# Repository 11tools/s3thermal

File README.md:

# s3thermal
a iray thermal camera controller pcb use Allwinner S3 

Can record thermal video. take thermal picture. may support night vision fusion in future

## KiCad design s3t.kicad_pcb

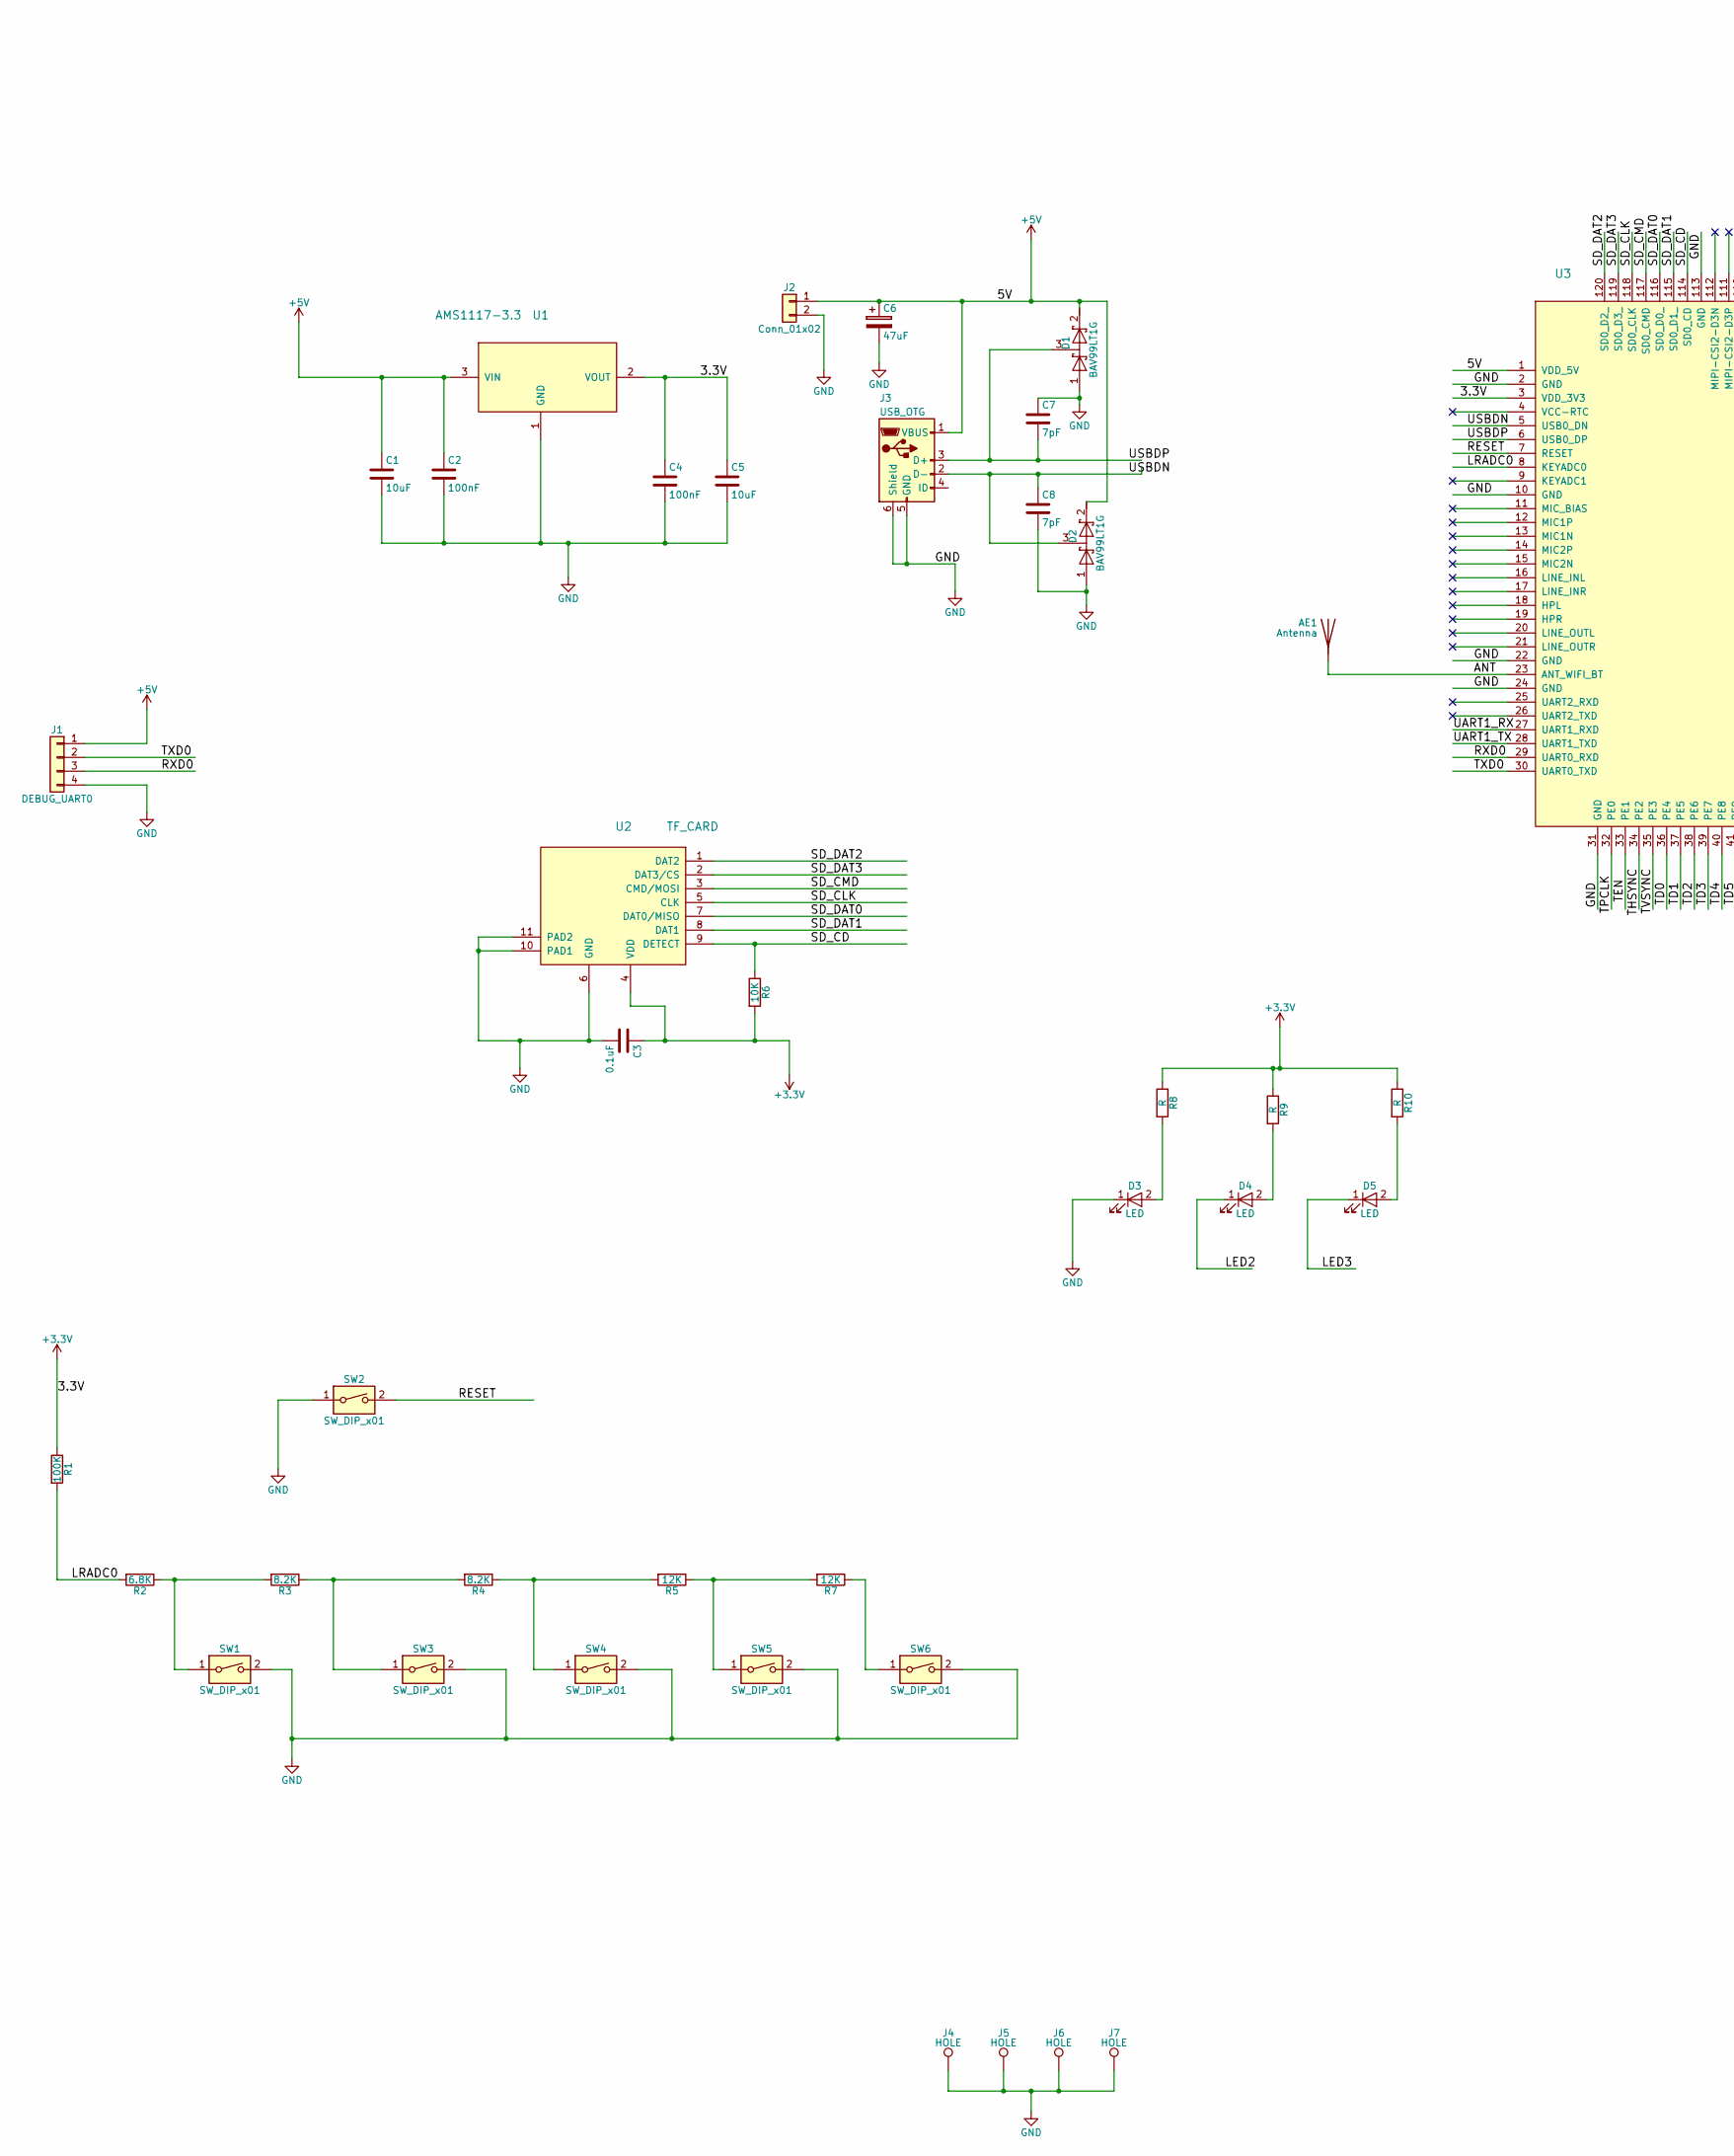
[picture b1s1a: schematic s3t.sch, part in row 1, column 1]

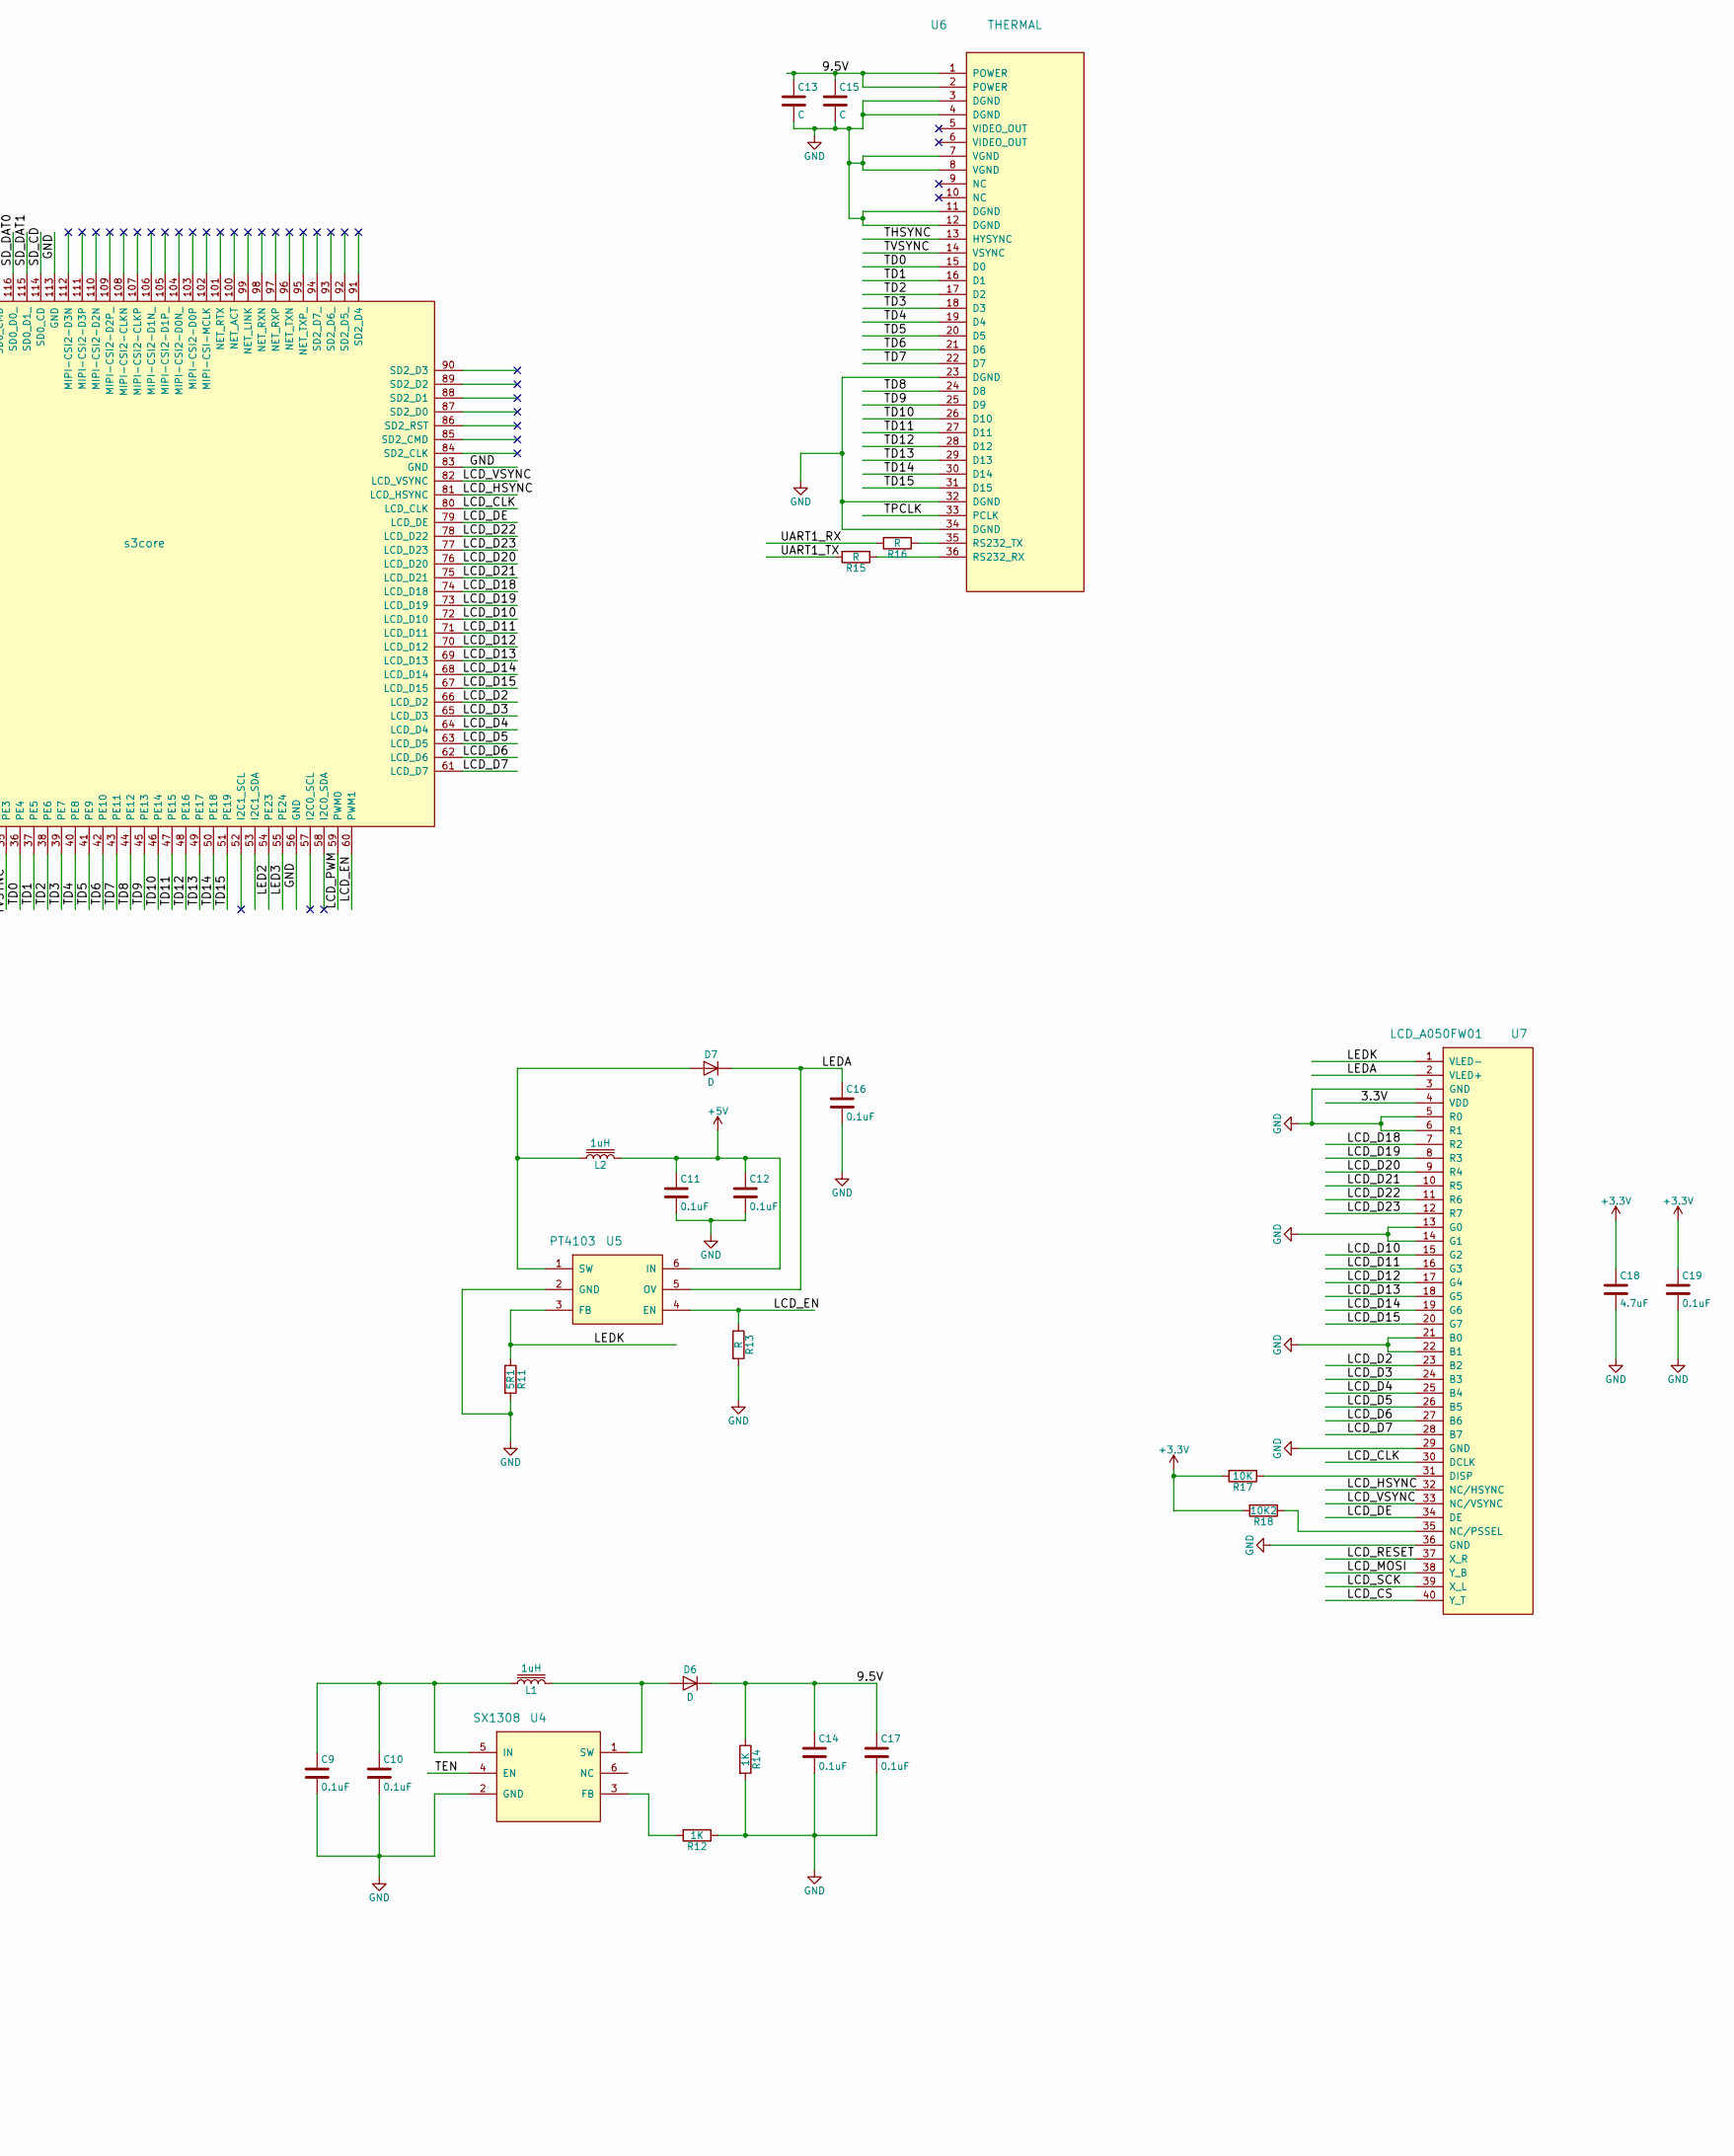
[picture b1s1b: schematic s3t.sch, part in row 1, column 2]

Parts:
AE1: Antenna
C1, C5: 10uF; C_0805
C2, C4: 100nF; C_0603
C3, C9, C10, C11, C12, C14, C16, C17, C19: 0.1uF; C_0603
C6: 47uF; CP_Radial_D8.0mm_P2.50mm
C7, C8: 7pF; C_0603
C13: C
C15: C; C_0603
C18: 4.7uF; C_0603
D1, D2: BAV99LT1G; SOT-23
D3, D4, D5: LED; LED_0805
D6, D7: D; D_SMA
J1: DEBUG_UART0; JST_EH_B04B-EH-A_04x2.50mm_Straight
J2: Conn_01x02; JST_EH_B02B-EH-A_02x2.50mm_Straight
J3: USB_OTG; USB_Mini-B
J4, J5, J6, J7: HOLE; hole
L1, L2: 1uH; L_1812
R1: 100K; R_0603
R2: 6.8K; R_0603
R3, R4: 8.2K; R_0603
R5, R7: 12K; R_0603
R6, R17: 10K; R_0603
R8, R9, R10, R13: R; R_0603
R11: 5R1; R_0603
R12, R14: 1K; R_0603
R15, R16: R; R_0805
R18: 10K2; C_0603
SW1, SW2, SW3, SW4, SW5, SW6: SW_DIP_x01; button
U1: AMS1117-3.3; SOT-223
U2: TF_CARD; tfcard
U3: s3core; S3Core
U4: SX1308; SOT-23-6
U5: PT4103; SOT-23-6
U6: THERMAL; Hirose_FH12-36S-0.5SH_1x36-1MP_P0.50mm_Horizontal
U7: LCD_A050FW01; Hirose_FH12-40S-0.5SH_1x40-1MP_P0.50mm_Horizontal

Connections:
+3V3: C3.1, C4.1, C5.1, C18.1, C19.1, R1.1, R6.2, R8.1, R9.1, R10.1, R17.2, R18.2, U1.2 (VOUT), U2.4 (VDD), U3.3 (VDD_3V3), U7.4 (VDD)
+5V: C1.1, C2.1, C6.1, C11.1, C12.1, D1.2 (K), D2.2 (K), J1.1, J2.1, J3.1 (VBUS), L2.1, U1.3 (VIN), U3.1 (VDD_5V), U5.6 (IN)
/9.5V: C13.1, C14.1, C15.1, C17.1, D6.1 (K), R14.1, U6.1 (POWER), U6.2 (POWER)
/ANT: AE1.1, U3.23 (ANT_WIFI_BT)
/LCD_CLK: U3.80 (LCD_CLK), U7.30 (DCLK)
/LCD_CS: U7.40 (Y_T)
/LCD_D2: U3.66 (LCD_D2), U7.23 (B2)
/LCD_D3: U3.65 (LCD_D3), U7.24 (B3)
/LCD_D4: U3.64 (LCD_D4), U7.25 (B4)
/LCD_D5: U3.63 (LCD_D5), U7.26 (B5)
/LCD_D6: U3.62 (LCD_D6), U7.27 (B6)
/LCD_D7: U3.61 (LCD_D7), U7.28 (B7)
/LCD_D10: U3.72 (LCD_D10), U7.15 (G2)
/LCD_D11: U3.71 (LCD_D11), U7.16 (G3)
/LCD_D12: U3.70 (LCD_D12), U7.17 (G4)
/LCD_D13: U3.69 (LCD_D13), U7.18 (G5)
/LCD_D14: U3.68 (LCD_D14), U7.19 (G6)
/LCD_D15: U3.67 (LCD_D15), U7.20 (G7)
/LCD_D18: U3.74 (LCD_D18), U7.7 (R2)
/LCD_D19: U3.73 (LCD_D19), U7.8 (R3)
/LCD_D20: U3.76 (LCD_D20), U7.9 (R4)
/LCD_D21: U3.75 (LCD_D21), U7.10 (R5)
/LCD_D22: U3.78 (LCD_D22), U7.11 (R6)
/LCD_D23: U3.77 (LCD_D23), U7.12 (R7)
/LCD_DE: U3.79 (LCD_DE), U7.34 (DE)
/LCD_EN: R13.1, U3.60 (PWM1), U5.4 (EN)
/LCD_HSYNC: U3.81 (LCD_HSYNC), U7.32 (NC/HSYNC)
/LCD_MOSI: U7.38 (Y_B)
/LCD_PWM: U3.59 (PWM0)
/LCD_RESET: U7.37 (X_R)
/LCD_SCK: U7.39 (X_L)
/LCD_VSYNC: U3.82 (LCD_VSYNC), U7.33 (NC/VSYNC)
/LED2: D4.1 (K), U3.54 (PE23)
/LED3: D5.1 (K), U3.55 (PE24)
/LEDA: C16.1, D7.1 (K), U5.5 (OV), U7.2 (VLED+)
/LEDK: R11.1, U5.3 (FB), U7.1 (VLED-)
/LRADC0: R1.2, R2.2, U3.8 (KEYADC0)
/RESET: SW2.2, U3.7 (RESET)
/RXD0: J1.3, U3.29 (UART0_RXD)
/SD_CD: R6.1, U2.9 (DETECT), U3.114 (SD0_CD)
/SD_CLK: U2.5 (CLK), U3.118 (SD0_CLK)
/SD_CMD: U2.3 (CMD/MOSI), U3.117 (SD0_CMD)
/SD_DAT0: U2.7 (DAT0/MISO), U3.116 (SD0_D0_)
/SD_DAT1: U2.8 (DAT1), U3.115 (SD0_D1_)
/SD_DAT2: U2.1 (DAT2), U3.120 (SD0_D2_)
/SD_DAT3: U2.2 (DAT3/CS), U3.119 (SD0_D3_)
/TD0: U3.36 (PE4), U6.15 (D0)
/TD1: U3.37 (PE5), U6.16 (D1)
/TD2: U3.38 (PE6), U6.17 (D2)
/TD3: U3.39 (PE7), U6.18 (D3)
/TD4: U3.40 (PE8), U6.19 (D4)
/TD5: U3.41 (PE9), U6.20 (D5)
/TD6: U3.42 (PE10), U6.21 (D6)
/TD7: U3.43 (PE11), U6.22 (D7)
/TD8: U3.44 (PE12), U6.24 (D8)
/TD9: U3.45 (PE13), U6.25 (D9)
/TD10: U3.46 (PE14), U6.26 (D10)
/TD11: U3.47 (PE15), U6.27 (D11)
/TD12: U3.48 (PE16), U6.28 (D12)
/TD13: U3.49 (PE17), U6.29 (D13)
/TD14: U3.50 (PE18), U6.30 (D14)
/TD15: U3.51 (PE19), U6.31 (D15)
/TEN: U3.33 (PE1), U4.4 (EN)
/THSYNC: U3.34 (PE2), U6.13 (HYSYNC)
/TPCLK: U3.32 (PE0), U6.33 (PCLK)
/TVSYNC: U3.35 (PE3), U6.14 (VSYNC)
/TXD0: J1.2, U3.30 (UART0_TXD)
/UART1_RX: R16.2, U3.27 (UART1_RXD)
/UART1_TX: R15.2, U3.28 (UART1_TXD)
/USBDN: C8.1, D2.3 (common), J3.2 (D-), U3.5 (USB0_DN)
/USBDP: C7.2, D1.3 (common), J3.3 (D+), U3.6 (USB0_DP)
GND: C1.2, C2.2, C3.2, C4.2, C5.2, C6.2, C7.1, C8.2, C9.2, C10.2, C11.2, C12.2, C13.2, C14.2, C15.2, C16.2, C17.2, C18.2, C19.2, D1.1 (A), D2.1 (A), D3.1 (K), J1.4, J2.2, J3.5 (GND), J3.6 (Shield), J4.1, J5.1, J6.1, J7.1, R11.2, R12.1, R13.2, R14.2, SW1.2, SW2.1, SW3.2, SW4.2, SW5.2, SW6.2, U1.1 (GND), U2.6 (GND), U2.10 (PAD1), U2.11 (PAD2), U3.2 (GND), U3.10 (GND), U3.22 (GND), U3.24 (GND), U3.31 (GND), U3.56 (GND), U3.83 (GND), U3.113 (GND), U4.2 (GND), U5.2 (GND), U6.3 (DGND), U6.4 (DGND), U6.7 (VGND), U6.8 (VGND), U6.11 (DGND), U6.12 (DGND), U6.23 (DGND), U6.32 (DGND), U6.34 (DGND), U7.3 (GND), U7.5 (R0), U7.6 (R1), U7.13 (G0), U7.14 (G1), U7.21 (B0), U7.22 (B1), U7.29 (GND), U7.36 (GND)
unnamed: C9.1, C10.1, L1.2, U4.5 (IN)
unnamed: D3.2 (A), R8.2
unnamed: D4.2 (A), R9.2
unnamed: D5.2 (A), R10.2
unnamed: D6.2 (A), L1.1, U4.1 (SW)
unnamed: D7.2 (A), L2.2, U5.1 (SW)
unnamed: R2.1, R3.2, SW1.1
unnamed: R3.1, R4.2, SW3.1
unnamed: R4.1, R5.2, SW4.1
unnamed: R5.1, R7.2, SW5.1
unnamed: R7.1, SW6.1
unnamed: R12.2, U4.3 (FB)
unnamed: R15.1, U6.36 (RS232_RX)
unnamed: R16.1, U6.35 (RS232_TX)
unnamed: R17.1, U7.31 (DISP)
unnamed: R18.1, U7.35 (NC/PSSEL)

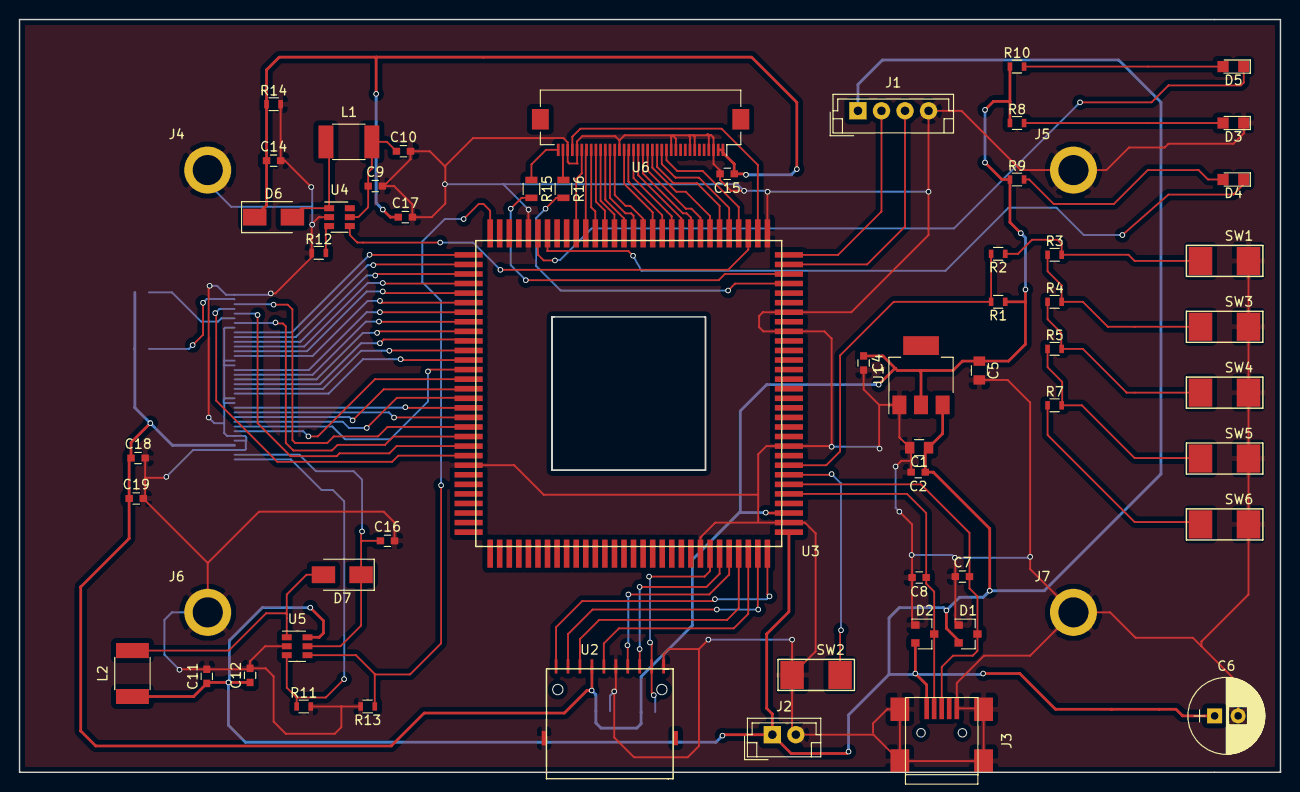
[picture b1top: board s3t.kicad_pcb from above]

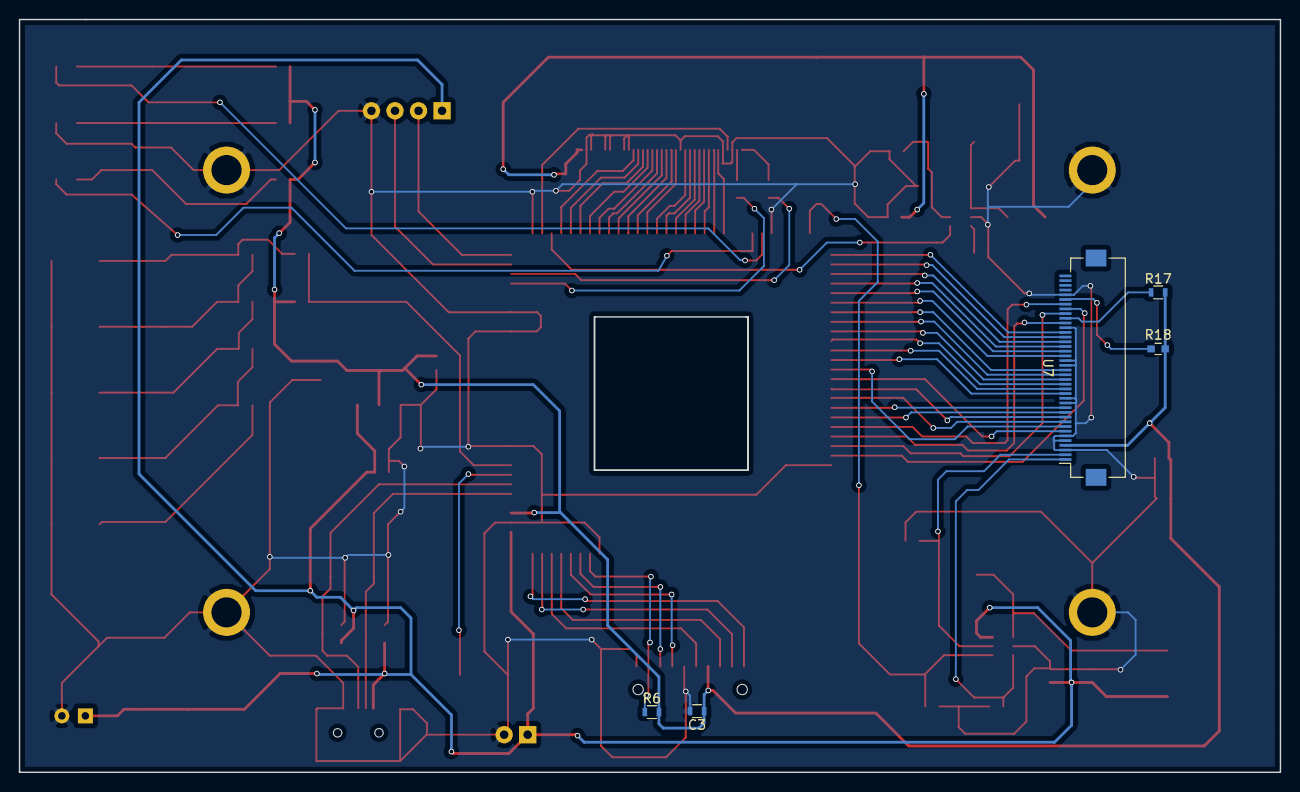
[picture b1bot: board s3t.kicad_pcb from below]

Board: 2 copper layers, 134.0 x 80.0 mm, 65 parts (5 on the bottom side), 82 nets.

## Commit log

2019-08-12 init s3 thermal camera pcb
2019-08-13 change TF card
2019-08-14 add some lib
2019-08-15 update pcb lib
2019-08-18 update pcb route
2019-08-19 update pcb
2019-08-20 finish pcb route
2019-08-21 finish all pcb and send to factory
